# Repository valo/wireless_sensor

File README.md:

# wireless_sensor
A wireless temperature sensor built with Arduino and nRF24L01 radio module

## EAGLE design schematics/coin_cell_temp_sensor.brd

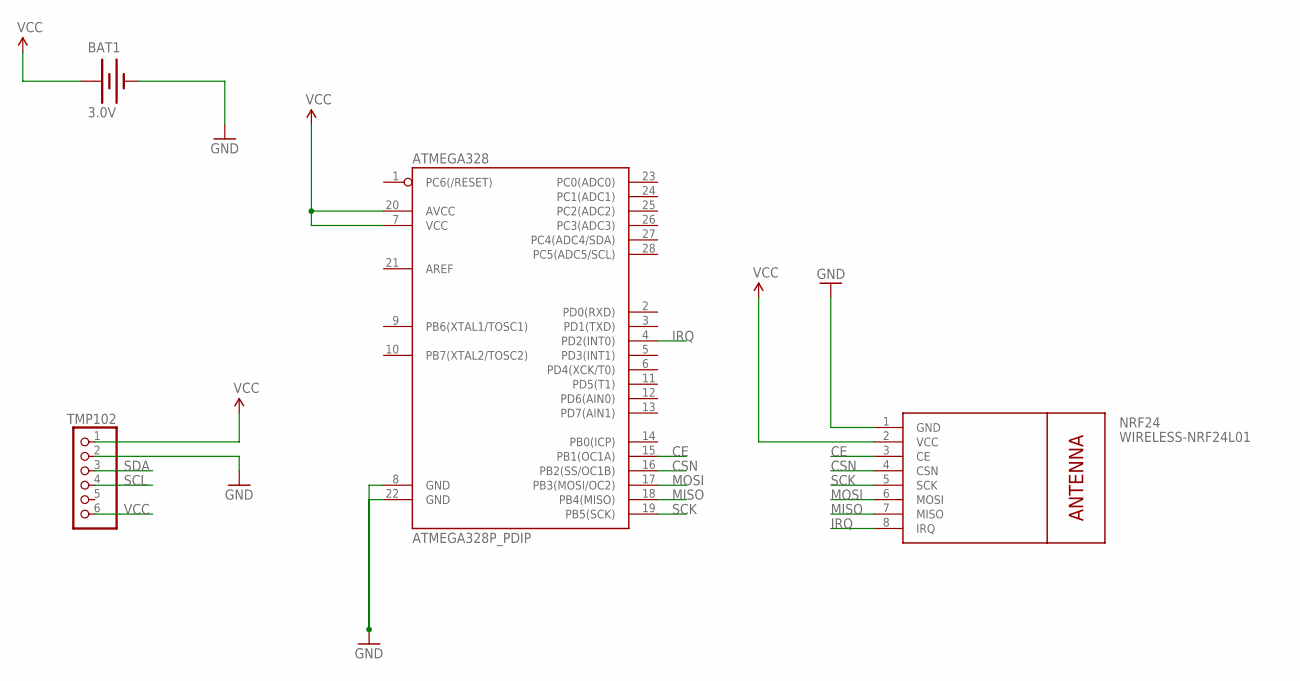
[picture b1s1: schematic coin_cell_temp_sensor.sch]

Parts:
ATMEGA328: ATMEGA328P_PDIP; DIL28-3
BAT1: 3.0V; BATTCON_245MM_PTH
NRF24: WIRELESS-NRF24L01
TMP102: PINHD-1X6; 1X06

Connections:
CE: ATMEGA328.15 (PB1(OC1A)), NRF24.3 (CE)
CSN: ATMEGA328.16 (PB2(SS/OC1B)), NRF24.4 (CSN)
GND: ATMEGA328.8 (GND), ATMEGA328.22 (GND), BAT1.2 (-), NRF24.1 (GND), TMP102.2
IRQ: ATMEGA328.4 (PD2(INT0)), NRF24.8 (IRQ)
MISO: ATMEGA328.18 (PB4(MISO)), NRF24.7 (MISO)
MOSI: ATMEGA328.17 (PB3(MOSI/OC2)), NRF24.6 (MOSI)
SCK: ATMEGA328.19 (PB5(SCK)), NRF24.5 (SCK)
SCL: TMP102.4
SDA: TMP102.3
VCC: ATMEGA328.7 (VCC), ATMEGA328.20 (AVCC), BAT1.3 (+), NRF24.2 (VCC), TMP102.1, TMP102.6

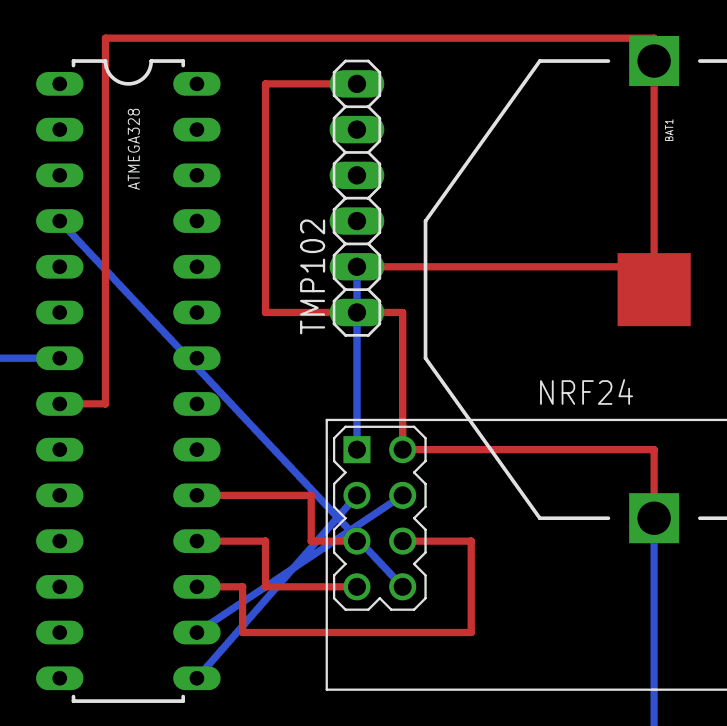
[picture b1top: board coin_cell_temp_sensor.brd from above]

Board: 2 copper layers, 4 parts (0 on the bottom side), 8 nets.

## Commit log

2015-10-08 Initial version of the sensor logic
    Includes unreliable transmission of the temperature data and AES128 encryption of the measurements.
2015-10-20 Initial version of the bettery powered wireless temperature sensor
2015-10-25 Updated the schematics with a routed PCB board
    Added a gitignore file.
    Added a fritzing schematic of the breadboard.

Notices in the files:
parts and their libraries:
SparkFun-Electromechanical: Licensing: Creative Commons ShareAlike 4.0 International - https://creativecommons.org/licenses/by-sa/4.0
diy-modules: Released under the Creative Commons Attribution 4.0 International License: http://creativecommons.org/licenses/by/4.0
